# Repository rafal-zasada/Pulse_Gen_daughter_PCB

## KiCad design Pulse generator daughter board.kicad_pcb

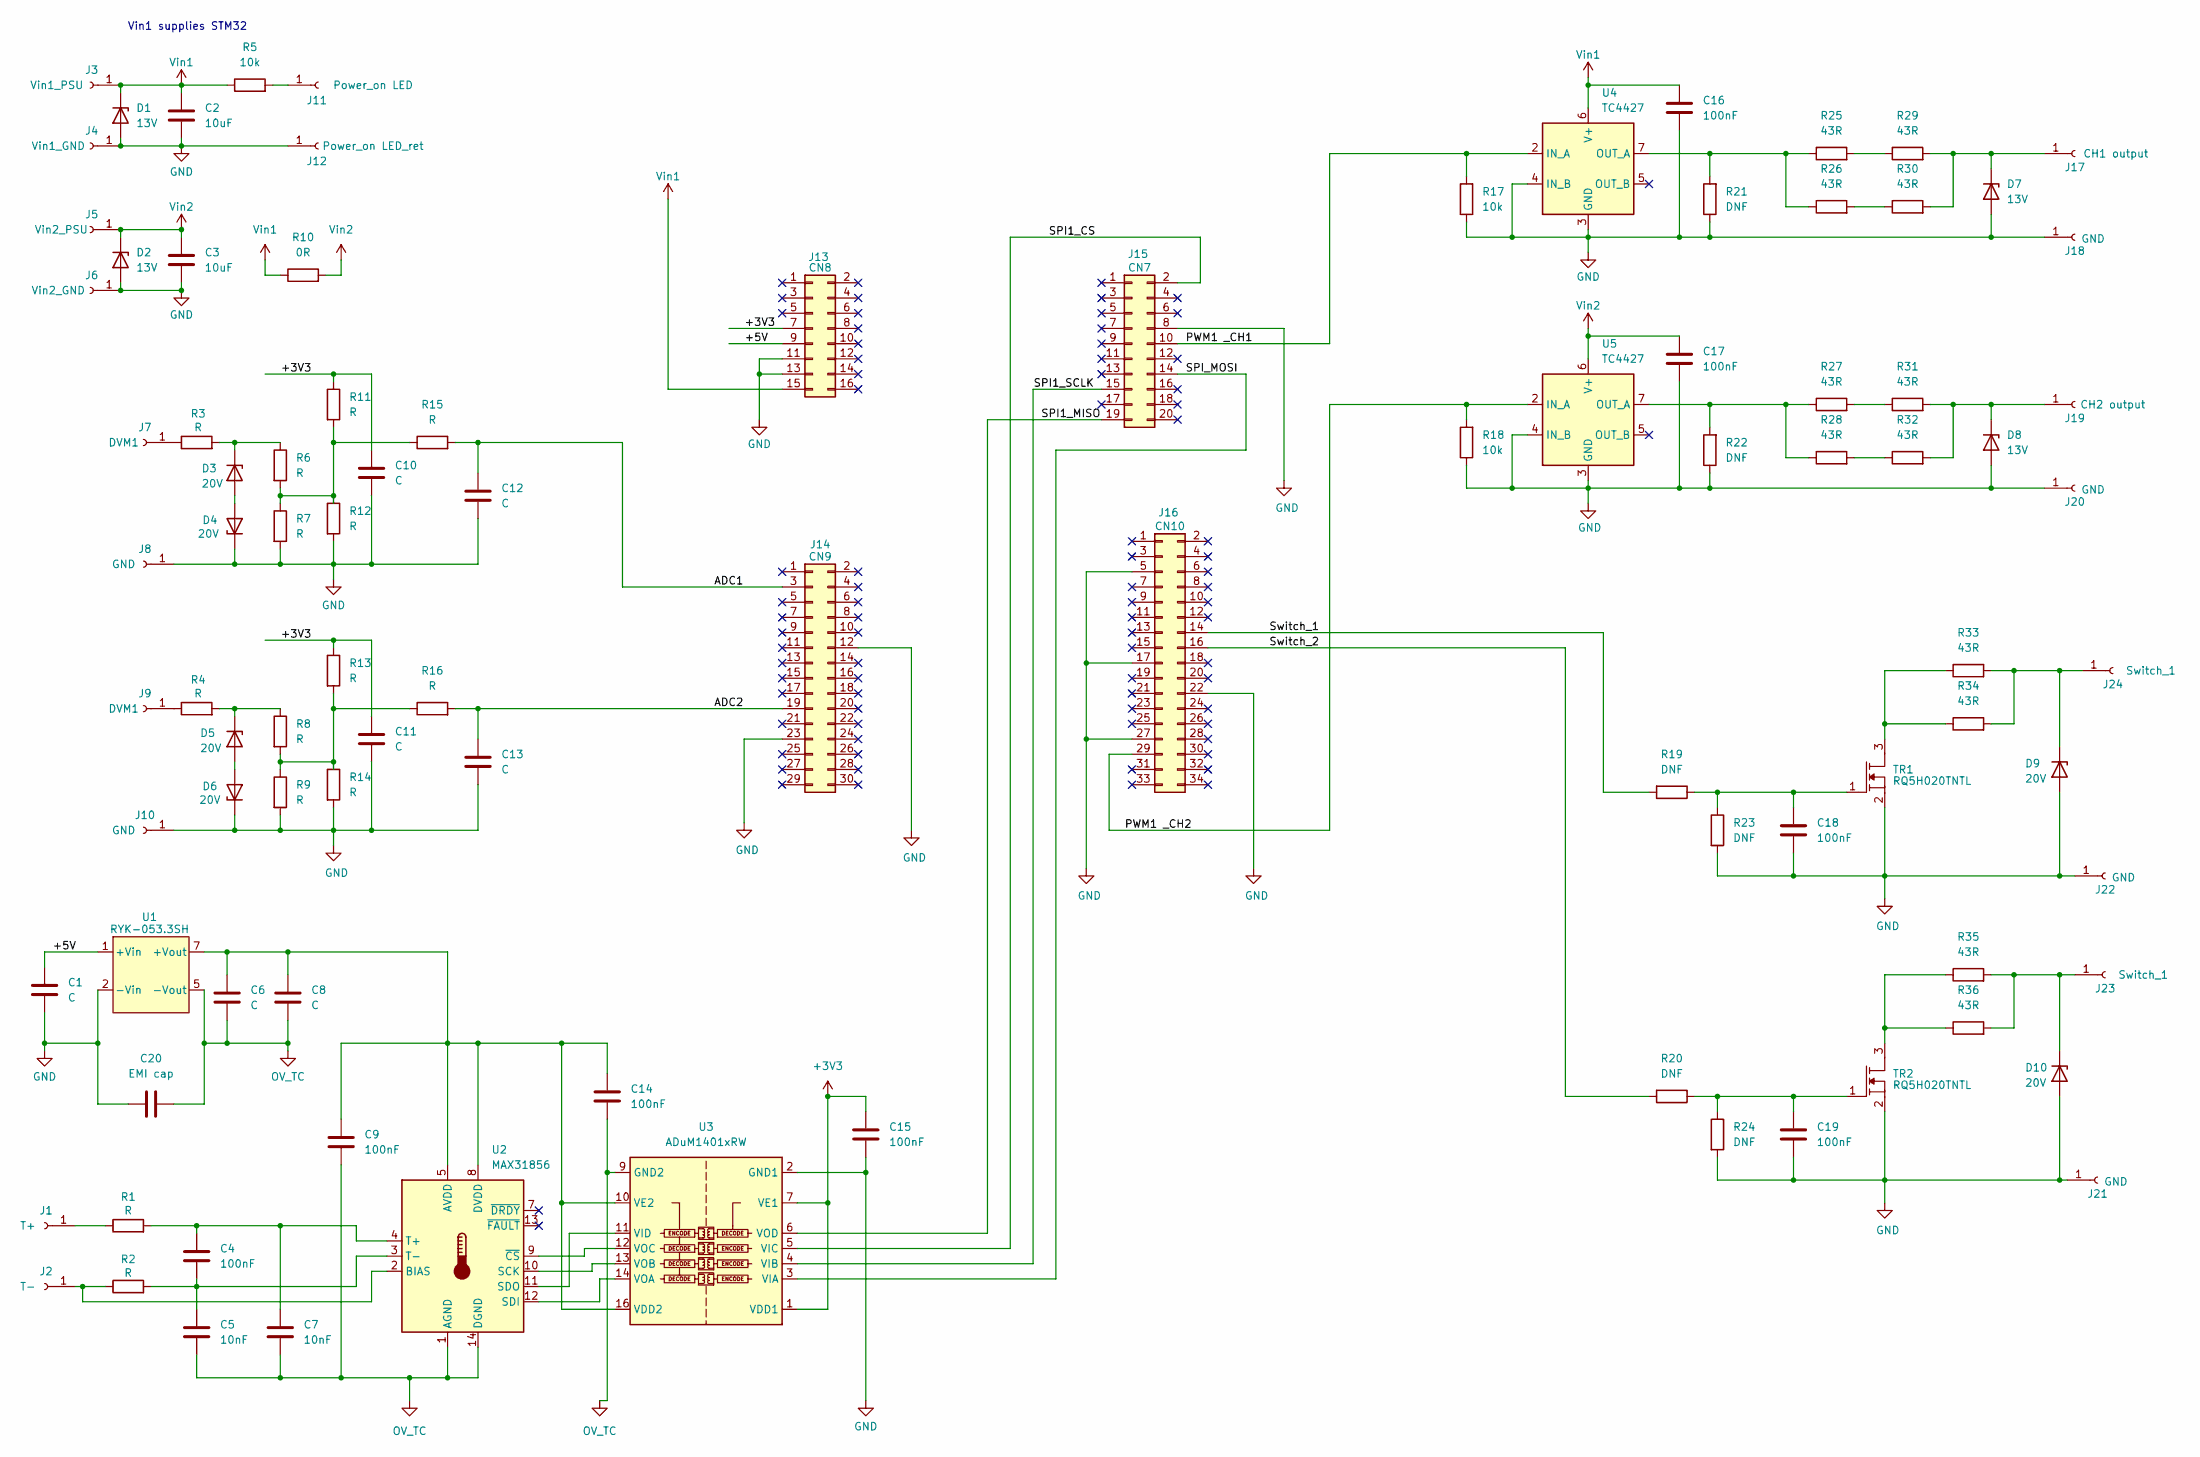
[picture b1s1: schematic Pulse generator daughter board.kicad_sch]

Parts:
C1, C6, C8, C10, C11, C12, C13: C; C_0805_2012Metric_Pad1.18x1.45mm_HandSolder
C2, C3: 10uF; C_0805_2012Metric_Pad1.18x1.45mm_HandSolder
C4, C9, C14, C15, C16, C17, C18, C19: 100nF; C_0805_2012Metric_Pad1.18x1.45mm_HandSolder
C5, C7: 10nF; C_0805_2012Metric_Pad1.18x1.45mm_HandSolder
C20: EMI cap; C_0805_2012Metric_Pad1.18x1.45mm_HandSolder
D1, D2, D7, D8: 13V; D_SMA_Handsoldering
D3, D4, D5, D6, D9, D10: 20V; D_SOD-323F
J1: T+; SolderWire-0.5sqmm_1x01_D0.9mm_OD2.1mm
J2: T-; SolderWire-0.5sqmm_1x01_D0.9mm_OD2.1mm
J3: Vin1_PSU; SolderWire-0.5sqmm_1x01_D0.9mm_OD2.1mm
J4: Vin1_GND; SolderWire-0.5sqmm_1x01_D0.9mm_OD2.1mm
J5: Vin2_PSU; SolderWire-0.5sqmm_1x01_D0.9mm_OD2.1mm
J6: Vin2_GND; SolderWire-0.5sqmm_1x01_D0.9mm_OD2.1mm
J7, J9: DVM1; SolderWire-0.5sqmm_1x01_D0.9mm_OD2.1mm
J8, J10, J18, J20, J21, J22: GND; SolderWire-0.5sqmm_1x01_D0.9mm_OD2.1mm
J11: Power_on LED; SolderWire-0.5sqmm_1x01_D0.9mm_OD2.1mm
J12: Power_on LED_ret; SolderWire-0.5sqmm_1x01_D0.9mm_OD2.1mm
J13: CN8; PinHeader_2x08_P2.54mm_Vertical
J14: CN9; PinHeader_2x15_P2.54mm_Vertical
J15: CN7; PinHeader_2x10_P2.54mm_Vertical
J16: CN10; PinHeader_2x17_P2.54mm_Vertical
J17: CH1 output; SolderWire-0.5sqmm_1x01_D0.9mm_OD2.1mm
J19: CH2 output; SolderWire-0.5sqmm_1x01_D0.9mm_OD2.1mm
J23, J24: Switch_1; SolderWire-0.5sqmm_1x01_D0.9mm_OD2.1mm
R1, R2, R3, R4, R6, R7, R8, R9, R11, R12, R13, R14, R15, R16: R; R_0805_2012Metric_Pad1.20x1.40mm_HandSolder
R5, R17, R18: 10k; R_0805_2012Metric_Pad1.20x1.40mm_HandSolder
R10: 0R; R_0805_2012Metric_Pad1.20x1.40mm_HandSolder
R19, R20, R21, R22, R23, R24: DNF; R_0805_2012Metric_Pad1.20x1.40mm_HandSolder
R25, R26, R27, R28, R29, R30, R31, R32, R33, R34, R35, R36: 43R; R_2512_6332Metric_Pad1.40x3.35mm_HandSolder
TR1, TR2: RQ5H020TNTL; SOT-346T
U1: RYK-053.3SH
U2: MAX31856; TSSOP-14_4.4x5mm_P0.65mm
U3: ADuM1401xRW; SOIC-16W_7.5x10.3mm_P1.27mm
U4, U5: TC4427; DIP-8_W7.62mm

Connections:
+3V3: C10.1, C11.1, C15.1, J13.7, R11.1, R13.1, U3.1 (VDD1), U3.7 (VE1)
/+5V: C1.1, J13.9, U1.1 (+Vin)
/ADC1: C12.1, J14.3, R15.2
/ADC2: C13.1, J14.19, R16.2
/PWM1 _CH1: J15.10, R17.2, U4.2 (IN_A)
/PWM1 _CH2: J16.29, R18.2, U5.2 (IN_A)
/SPI1_CS: J15.2, U3.5 (VIC)
/SPI1_MISO: J15.19, U3.6 (VOD)
/SPI1_SCLK: J15.15, U3.4 (VIB)
/SPI_MOSI: J15.14, U3.3 (VIA)
/Switch_1: J16.14, R19.2
/Switch_2: J16.16, R20.2
GND: C1.2, C2.2, C3.2, C10.2, C11.2, C12.2, C13.2, C15.2, C16.2, C17.2, C18.2, C19.2, C20.1, D1.2 (A), D2.2 (A), D4.1 (K), D6.1 (K), D7.2 (A), D8.2 (A), D9.2 (A), D10.2 (A), J4.1, J6.1, J8.1, J10.1, J12.1, J13.11, J13.13, J14.12, J14.23, J15.8, J16.5, J16.17, J16.22, J16.27, J18.1, J20.1, J21.1, J22.1, R7.2, R9.2, R12.2, R14.2, R17.1, R18.1, R21.1, R22.1, R23.2, R24.2, TR1.2, TR2.2, U1.2 (-Vin), U3.2 (GND1), U3.8 (GND1), U4.3 (GND), U4.4 (IN_B), U5.3 (GND), U5.4 (IN_B)
unnamed: C18.1, R19.1, R23.1, TR1.1
unnamed: C19.1, R20.1, R24.1, TR2.1
unnamed: D3.2 (A), D4.2 (A)
unnamed: D3.1 (K), R3.2, R6.1
unnamed: D5.2 (A), D6.2 (A)
unnamed: D5.1 (K), R4.2, R8.1
unnamed: D7.1 (K), J17.1, R29.2, R30.2
unnamed: D8.1 (K), J19.1, R31.2, R32.2
unnamed: D9.1 (K), J24.1, R33.2, R34.2
unnamed: D10.1 (K), J23.1, R35.2, R36.2
unnamed: J1.1, R1.1
unnamed: J2.1, R2.1, U2.2 (BIAS)
unnamed: J7.1, R3.1
unnamed: J9.1, R4.1
unnamed: J11.1, R5.2
unnamed: R6.2, R7.1, R11.2, R12.1, R15.1
unnamed: R8.2, R9.1, R13.2, R14.1, R16.1
unnamed: R25.2, R29.1
unnamed: R26.2, R30.1
unnamed: R27.2, R31.1
unnamed: R28.2, R32.1
unnamed: R33.1, R34.1, TR1.3
unnamed: R35.1, R36.1, TR2.3
unnamed: C6.1, C8.1, C9.1, C14.1, U1.7 (+Vout), U2.5 (AVDD), U2.8 (DVDD), U3.10 (VE2), U3.16 (VDD2)
unnamed: U2.10 (SCK), U3.13 (VOB)
unnamed: U2.12 (SDI), U3.14 (VOA)
unnamed: U2.11 (SDO), U3.11 (VID)
unnamed: C4.1, C7.1, R1.2, U2.4 (T+)
unnamed: C4.2, C5.1, R2.2, U2.3 (T-)
unnamed: U2.9 (~CS), U3.12 (VOC)
unnamed: R21.2, R25.1, R26.1, U4.7 (OUT_A)
unnamed: R22.2, R27.1, R28.1, U5.7 (OUT_A)
OV_TC: C5.2, C6.2, C7.2, C8.2, C9.2, C14.2, C20.2, U1.5 (-Vout), U2.1 (AGND), U2.14 (DGND), U3.9 (GND2), U3.15 (GND2)
Vin1: C2.1, C16.1, D1.1 (K), J3.1, J13.15, R5.1, R10.1, U4.6 (V+)
Vin2: C3.1, C17.1, D2.1 (K), J5.1, R10.2, U5.6 (V+)

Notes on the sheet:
Vin1 supplies STM32

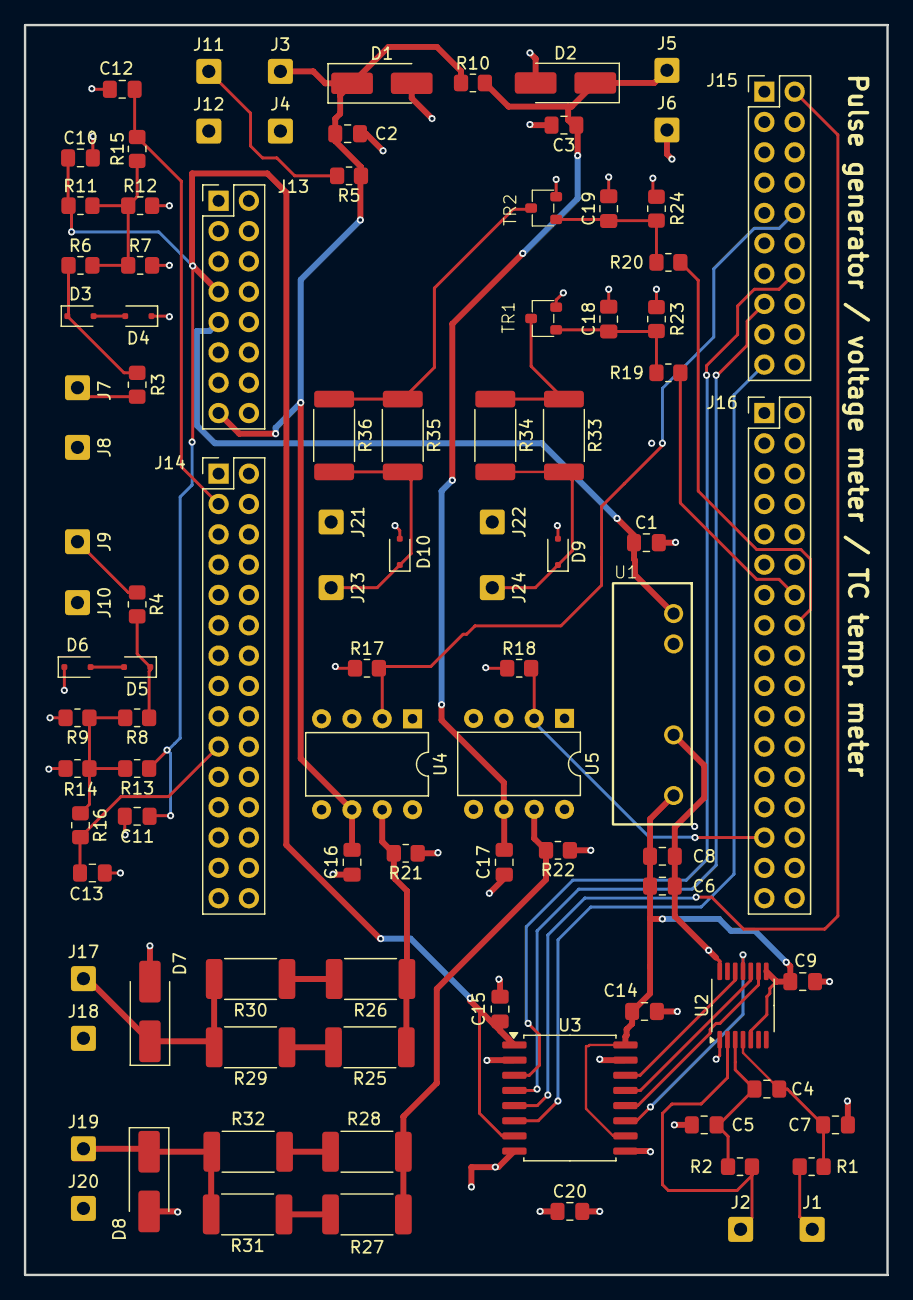
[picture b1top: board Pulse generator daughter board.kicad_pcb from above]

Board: 4 copper layers, 72.2 x 104.7 mm, 97 parts (0 on the bottom side), 48 nets.

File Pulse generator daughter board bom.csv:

"Reference","Value","Datasheet","Footprint","Qty","DNP"
"C1,C2,C3,C6,C8,C10,C11,C12,C13","C","~","Capacitor_SMD:C_0805_2012Metric_Pad1.18x1.45mm_HandSolder","9",""
"C4,C9,C14,C15,C16,C17,C18,C19","100nF","~","Capacitor_SMD:C_0805_2012Metric_Pad1.18x1.45mm_HandSolder","8",""
"C5,C7","10nF","~","Capacitor_SMD:C_0805_2012Metric_Pad1.18x1.45mm_HandSolder","2",""
"C20","EMI cap","~","Capacitor_SMD:C_0805_2012Metric_Pad1.18x1.45mm_HandSolder","1",""
"D1,D2,D7,D8","13V","~","Diode_SMD:D_SMA_Handsoldering","4",""
"D3,D4,D5,D6,D9,D10","20V","~","Diode_SMD:D_SOD-323F","6",""
"J1","T+","~","Connector_Wire:SolderWire-0.5sqmm_1x01_D0.9mm_OD2.1mm","1",""
"J2","T-","~","Connector_Wire:SolderWire-0.5sqmm_1x01_D0.9mm_OD2.1mm","1",""
"J3","Vin1_PSU","~","Connector_Wire:SolderWire-0.5sqmm_1x01_D0.9mm_OD2.1mm","1",""
"J4","Vin1_GND","~","Connector_Wire:SolderWire-0.5sqmm_1x01_D0.9mm_OD2.1mm","1",""
"J5","Vin2_PSU","~","Connector_Wire:SolderWire-0.5sqmm_1x01_D0.9mm_OD2.1mm","1",""
"J6","Vin2_GND","~","Connector_Wire:SolderWire-0.5sqmm_1x01_D0.9mm_OD2.1mm","1",""
"J7,J9","DVM1","~","Connector_Wire:SolderWire-0.5sqmm_1x01_D0.9mm_OD2.1mm","2",""
"J8,J10,J18,J20,J21,J22","GND","~","Connector_Wire:SolderWire-0.5sqmm_1x01_D0.9mm_OD2.1mm","6",""
"J11","Power_on LED","~","Connector_Wire:SolderWire-0.5sqmm_1x01_D0.9mm_OD2.1mm","1",""
"J12","Power_on LED_ret","~","Connector_Wire:SolderWire-0.5sqmm_1x01_D0.9mm_OD2.1mm","1",""
"J13","CN8","~","Connector_PinHeader_2.54mm:PinHeader_2x08_P2.54mm_Vertical","1",""
"J14","CN9","~","Connector_PinHeader_2.54mm:PinHeader_2x15_P2.54mm_Vertical","1",""
"J15","CN7","~","Connector_PinHeader_2.54mm:PinHeader_2x10_P2.54mm_Vertical","1",""
"J16","CN10","~","Connector_PinHeader_2.54mm:PinHeader_2x17_P2.54mm_Vertical","1",""
"J17","CH1 output","~","Connector_Wire:SolderWire-0.5sqmm_1x01_D0.9mm_OD2.1mm","1",""
"J19","CH2 output","~","Connector_Wire:SolderWire-0.5sqmm_1x01_D0.9mm_OD2.1mm","1",""
"J23,J24","Switch_1","~","Connector_Wire:SolderWire-0.5sqmm_1x01_D0.9mm_OD2.1mm","2",""
"R1,R2,R3,R4,R6,R7,R8,R9,R11,R12,R13,R14,R15,R16","R","~","Resistor_SMD:R_0805_2012Metric_Pad1.20x1.40mm_HandSolder","14",""
"R5,R17,R18","10k","~","Resistor_SMD:R_0805_2012Metric_Pad1.20x1.40mm_HandSolder","3",""
"R10","0R","~","Resistor_SMD:R_0805_2012Metric_Pad1.20x1.40mm_HandSolder","1",""
"R19,R20,R21,R22,R23,R24","DNF","~","Resistor_SMD:R_0805_2012Metric_Pad1.20x1.40mm_HandSolder","6",""
"R25,R26,R27,R28,R29,R30,R31,R32,R33,R34,R35,R36","43R","~","Resistor_SMD:R_2512_6332Metric_Pad1.40x3.35mm_HandSolder","12",""
"TR1,TR2","RQ5H020TNTL","","Rafal:SOT-346T","2",""
"U1","RYK-053.3SH","","Rafal:RYK-053.3SH","1",""
"U2","MAX31856","https://datasheets.maximintegrated.com/en/ds/MAX31856.pdf","Package_SO:TSSOP-14_4.4x5mm_P0.65mm","1",""
"U3","ADuM1401xRW","https://www.analog.com/media/en/technical-documentation/data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","Package_SO:SOIC-16W_7.5x10.3mm_P1.27mm","1",""
"U4,U5","TC4427","http://ww1.microchip.com/downloads/en/DeviceDoc/mic4426.pdf","Package_DIP:DIP-8_W7.62mm","2",""

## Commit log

2024-11-23 PWMs and DWMs done
2024-11-24 Progress 2 on schematic and PCB
2024-11-29 Progress on PCB 29.11.2024
2024-11-30 Connector position locked + some more progress
2024-12-02 Positioning done
2024-12-04 LAyout finished
2024-12-04 LAyout finished + small corrections
2024-12-11 4 unconnected pads on PCB fixed
